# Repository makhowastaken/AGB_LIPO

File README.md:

# AGB_LIPO

THESE MAY STILL REQUIRE MORE TWEAKS BEFORE THEY WORK PROPERLY! Please do not make one if you are not afraid of having to modify the board to get it to work. See the video linked down below for more information. The files have since been updated but not yet tested. 

LiPo adapter for Game Boy Advance. Same concept as my AGS adapters: https://github.com/makhowastaken/AGS_LIPO

* Uses these battery terminals: https://il.farnell.com/keystone/5330/battery-contact-aaa-aaaa-n-12v/dp/1888418
but due to the absurd cost of shipping, I bought these instead: https://www.aliexpress.com/item/32884289489.html
* a standard TP4056 module (Micro USB or USB C): https://www.aliexpress.com/item/32649780468.html
* and pretty much whatever diode you can get your hands on: https://www.aliexpress.com/item/32664545131.html

I got my boards in and had to make some alterations to get them to fit better. I ordered new battery terminals again but I did try with some of the terminals I already had: https://youtu.be/GEl8VRI-Jl0

Per a recommendation from a user on my youtube channel (thanks Jonathan M Santos), it looks I've found suitable batteries that will fit with no or minimal modification. 103040 (1200mAh) batteries fit with absolutely zero modification to the AGB, and 103048 (1455mAh) batteries fit with a small trim to the plastic in the battery compartment. See this video (timestamped) for more detail: https://youtu.be/A86y9P2SIq0?t=337

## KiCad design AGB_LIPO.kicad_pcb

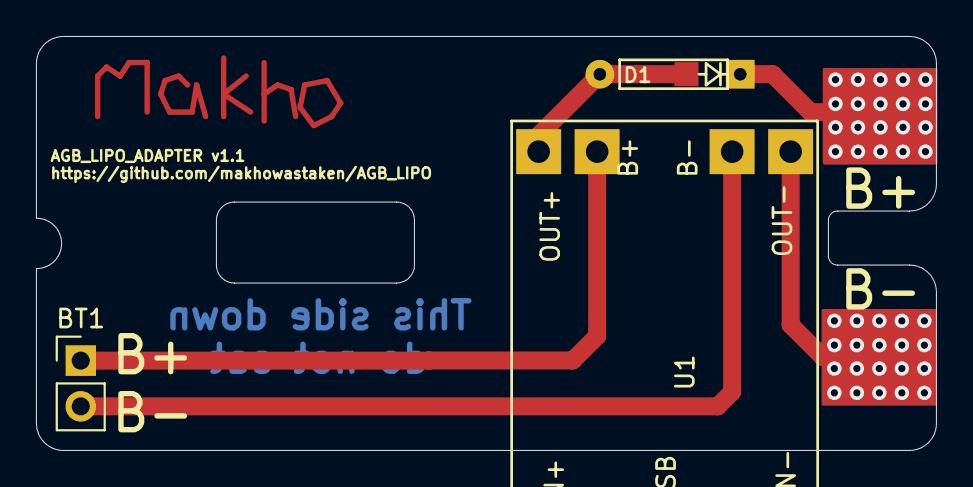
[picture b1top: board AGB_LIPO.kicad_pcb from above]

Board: 2 copper layers, 50.0 x 23.0 mm, 3 parts (0 on the bottom side), 3 nets.

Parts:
BT1: Battery_Cell; PinHeader_1x02_P2.54mm_Vertical
D1: D; Diode-hybrid-3pad
U1: tp4056_board-tp4056; 4056E_LiIon_loader

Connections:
unnamed: BT1.1, U1.3
unnamed: BT1.2, U1.4
unnamed: D1.2, U1.5

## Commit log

2020-02-14 Add files via upload
    tweaked the dimensions to fit better
2020-02-15 Create LICENSE
2020-05-14 Add files via upload
    modified placement of components on board, updated silkscreen and soldermask to represent updated files
2020-05-14 Add files via upload
    moved items on silkscreen to prevent overlap
